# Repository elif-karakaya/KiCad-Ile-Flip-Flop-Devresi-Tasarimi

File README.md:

# KiCad İle Flip Flop Devresi Tasarımı

Bu çalışmada KiCad programında Flip Flop devresi tasarlanmıştır. GitHub Desktop kullanarak projeyi kolayca klonlayabilir, geliştirme yapabilir ve katkıda bulunabilirsiniz.

## 🚀 Başlarken

### 1. Bu projenin çalışması

Bu projede devrenin girişine uygulanan sinyal değişmediği sürece çıkış durumunun aynı şekilde korunması amaçlanmıştır.

### Devrenin PCB Tasarım Görüntüsü

### Devrenin Üç Boyutlu PCB Tasarım Görüntüsü

### 2. Bu projeyi kendi bilgisayarınıza klonlayın

GitHub Desktop kullanıyorsanız:

1. "Code" butonuna tıklayın
2. "Open with GitHub Desktop" seçeneğini seçin
3. GitHub Desktop üzerinden dizini seçin ve "Clone" butonuna tıklayın

Alternatif olarak komut satırı ile:

```bash
git clone https://github.com/elif-karakaya/KiCad-Ile-Flip-Flop-Devresi-Tasarimi.git

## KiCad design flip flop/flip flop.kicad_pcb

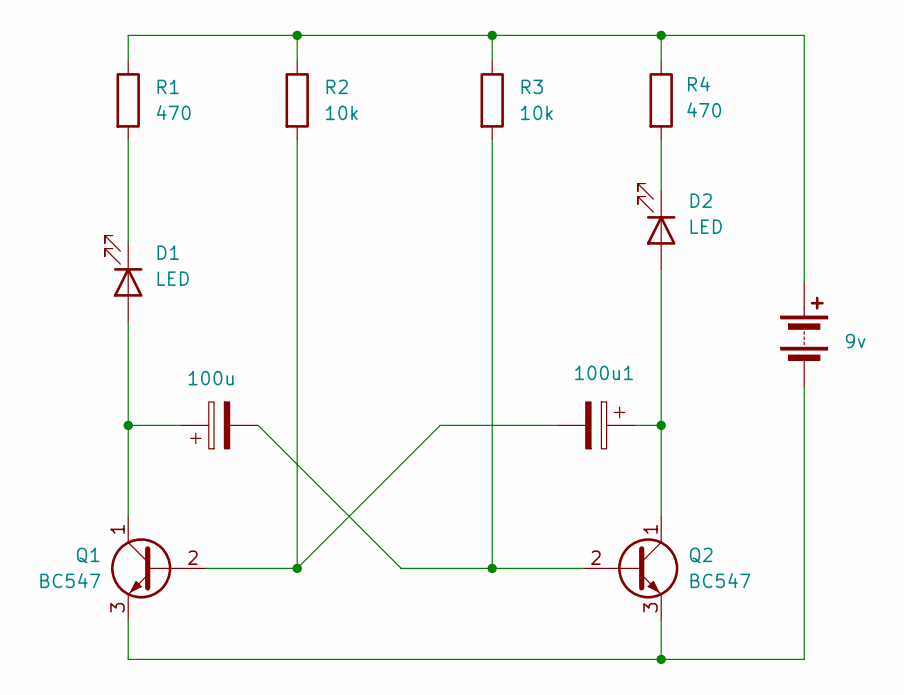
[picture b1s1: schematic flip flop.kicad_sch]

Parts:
100u1: C_Polarized; C_Rect_L7.2mm_W5.5mm_P5.00mm_FKS2_FKP2_MKS2_MKP2
BT1: 9v; PinSocket_1x02_P2.54mm_Horizontal
C1: 100u; C_Rect_L7.2mm_W5.5mm_P5.00mm_FKS2_FKP2_MKS2_MKP2
D1, D2: LED; LED_D3.0mm
Q1, Q2: BC547; TO-92_Inline
R1, R4: 470; R_Axial_DIN0204_L3.6mm_D1.6mm_P5.08mm_Horizontal
R2, R3: 10k; R_Axial_DIN0204_L3.6mm_D1.6mm_P5.08mm_Horizontal

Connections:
unnamed: BT1.1 (+), R1.1, R2.1, R3.1, R4.1
unnamed: BT1.2 (-), Q1.3 (E), Q2.3 (E)
unnamed: C1.1, D1.2 (A), Q1.1 (C)
unnamed: D1.1 (K), R1.2
unnamed 4: 100u1.1, D2.2 (A), Q2.1 (C); also elsewhere on the board
unnamed: D2.1 (K), R4.2
unnamed 6: 100u1.2, Q1.2 (B), R2.2; also elsewhere on the board
unnamed: C1.2, Q2.2 (B), R3.2

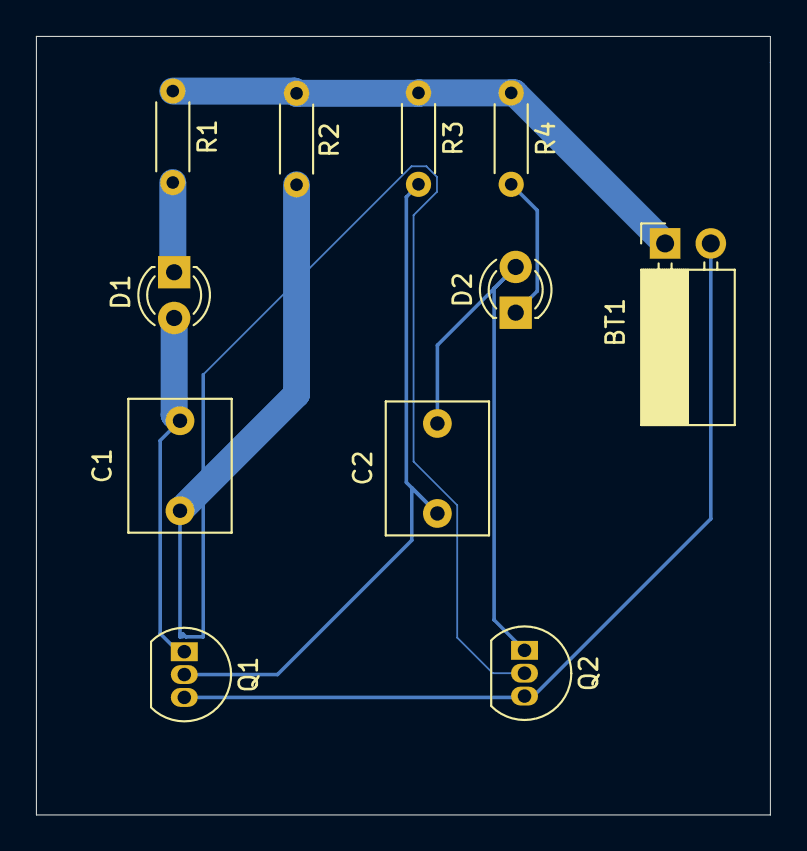
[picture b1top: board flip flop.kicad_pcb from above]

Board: 2 copper layers, 40.8 x 43.2 mm, 11 parts (0 on the bottom side), 8 nets.

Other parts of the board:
C2: 100u; C_Rect_L7.2mm_W5.5mm_P5.00mm_FKS2_FKP2_MKS2_MKP2

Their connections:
unnamed 4: C2.1; also elsewhere on the board
unnamed 6: C2.2; also elsewhere on the board

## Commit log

2025-07-18 Flip Flop devre klasörü eklendi.
